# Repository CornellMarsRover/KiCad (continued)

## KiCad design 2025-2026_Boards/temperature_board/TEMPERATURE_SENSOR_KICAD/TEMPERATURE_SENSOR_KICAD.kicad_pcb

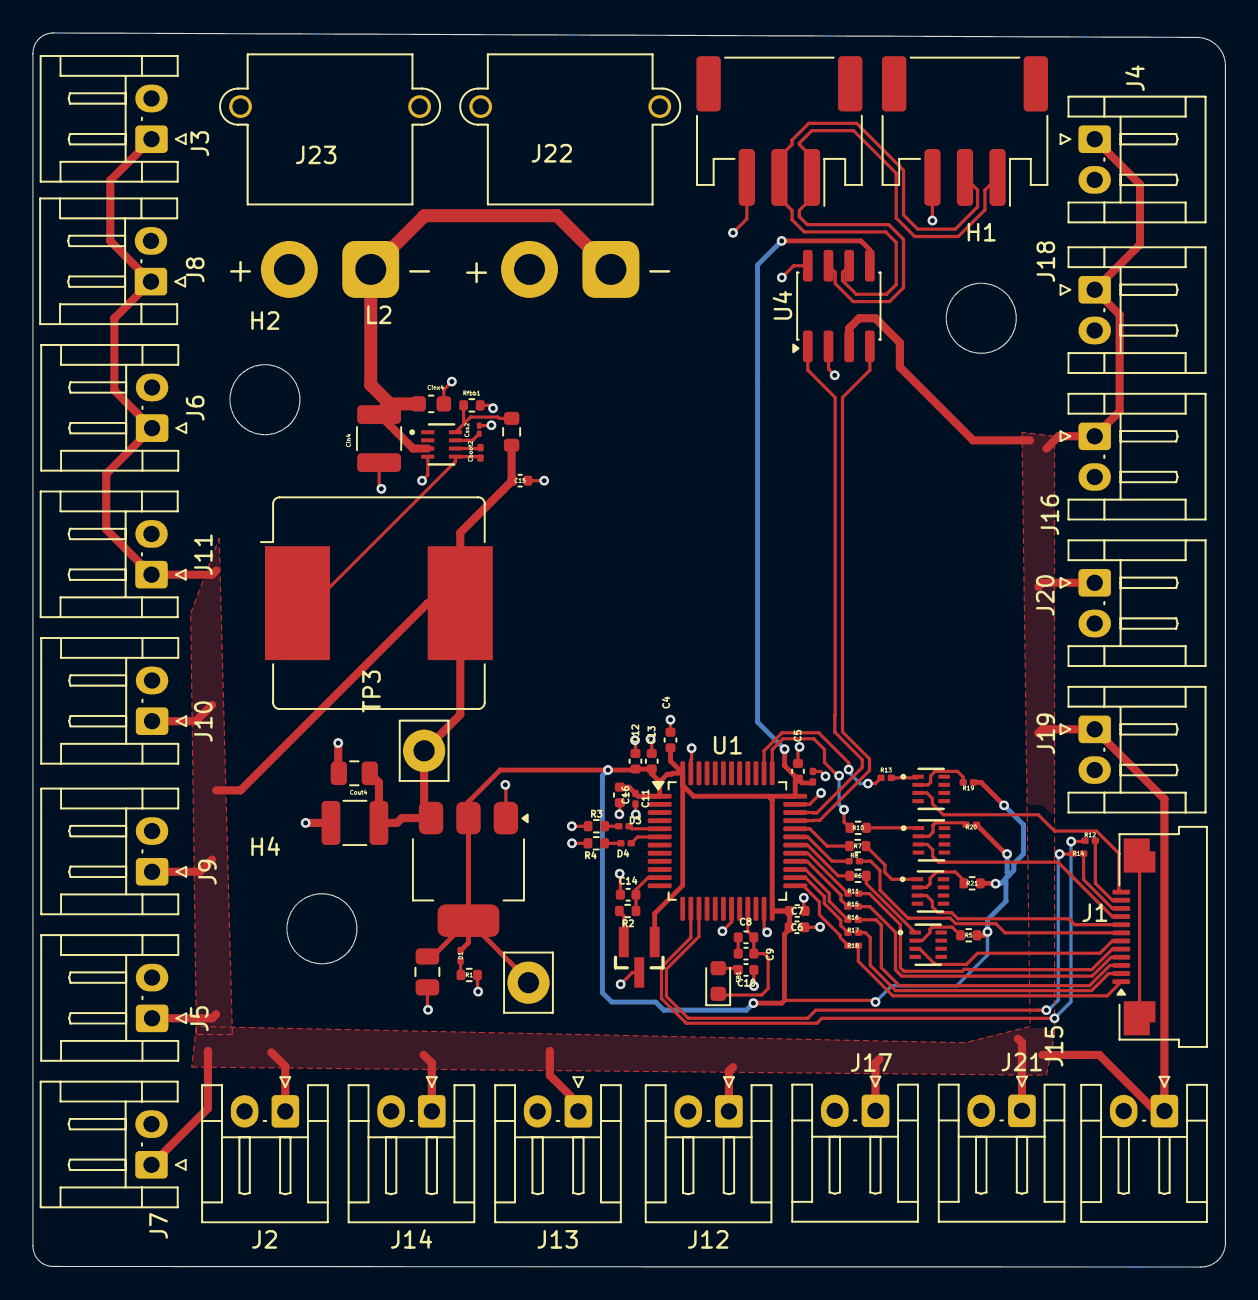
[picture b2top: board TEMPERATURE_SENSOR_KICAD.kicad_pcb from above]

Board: 2 copper layers, 73.3 x 75.8 mm, 87 parts (0 on the bottom side), 54 nets.

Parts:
C1, C2: 22u; C_0805_2012Metric
C3, C11: 10u; C_0201_0603Metric
C4, C5, C6, C7, C12, C13, C15, C16: 100n; C_0402_1005Metric
C8, C14: 10n; C_0402_1005Metric
C9, C10: 1u; C_0402_1005Metric
Cboot2: 33n; C_0201_0603Metric
Cin4: 10u; C_1210_3225Metric
Cinx4: 100n; C_0603_1608Metric
Cout4: 47u; C_1210_3225Metric
Css2: 33n; C_01005_0402Metric
D1: LED; C_0201_0603Metric
D3: DEBUG LED 1; C_0201_0603Metric
D4: DEBUG LED 2; C_0201_0603Metric
FB1: 120R; LED_0603_1608Metric
H1, H2, H4: MountingHole; MountingHole_4.3mm_M4
J1: LCD Connector Pinout; Amphenol_F32Q-1A7x1-11012_1x12-1MP_P0.5mm_Horizontal
J2, J3, J4, J5, J6, J7, J8, J9, J10, J11, J12, J13, J14, J15, J16, J17, J18, J19, J20, J21: Conn_01x02_Pin; JST_EH_S2B-EH_1x02_P2.50mm_Horizontal
J22, J23: Conn_01x02_Pin; AMASS_XT30PW-M_1x02_P2.50mm_Horizontal
J24, J25: Conn_01x03_Socket; JST_PH_S3B-PH-SM4-TB_1x03-1MP_P2.00mm_Horizontal
L2: 10u; L_Bourns_SRR1208_12.7x12.7mm
Q1, Q3, Q4: Q_NPN_BCE; SOT8_DRL_TEX
Q5: Q_PNP_BCE; SOT8_DRL_TEX
R1, R3, R4: 1k5; R_0402_1005Metric
R2, R6, R7, R10: 10k; R_0402_1005Metric
R5, R21: 55; R_0402_1005Metric
R8, R11, R12, R14, R15, R16, R17, R18: 80; R_0201_0603Metric
R13: 10k; R_0201_0603Metric
R19, R20: 55; R_0201_0603Metric
Rfbb1: 10k; R_0402_1005Metric
Rfbt1: 52.3k; R_0603_1608Metric
TP1, TP3: TestPoint; Pin_D1.3mm_L10.0mm_W3.5mm_Flat
U1: STM32G431CBT6; LQFP-48_7x7mm_P0.5mm
U2: TMP235A4DBZR; DBZ0003A-IPC_A
U3: AMS1117-3.3; SOT-223-3_TabPin2
U4: TCAN1057AEV-Q1; SOIC-8_3.9x4.9mm_P1.27mm
U5: TPS62932DRLR; SOT8_DRL_TEX-M

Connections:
5V: C1.1, C15.1, Cout4.1, J2.1, J3.1, J4.1, J5.1, J6.1, J7.1, J8.1, J9.1, J10.1, J11.1, J12.1, J13.1, J14.1, J15.1, J16.1, J17.1, J18.1, J19.1, J20.1, J21.1, L2.2, Rfbt1.1, TP3.1, U3.3 (VI), U4.3 (VCC)
28V: Cin4.1, Cinx4.1, J22.1, J23.1, U5.3 (VIN)
+3.3V: C2.1, C3.1, C4.1, C5.1, C6.1, C7.1, C11.1, C12.1, C13.1, C16.1, D1.2 (A), R5.1, R19.1, R20.1, R21.1, TP1.1, U1.1 (VBAT), U1.24 (VDD), U1.36 (VDD), U1.48 (VDD), U2.1 (VDD), U3.2 (VO), U4.5 (VIO)
+3.3VA: C8.1, C9.1, FB1.1, U1.21 (VDDA)
/PWR_LED_K: D1.1 (K), R1.1
CAN+: J24.1, J25.1, U4.7 (CANH)
CAN-: J24.2, J25.2, U4.6 (CANL)
FDCAN_+: U1.34 (PA12), U4.1 (TXD)
FDCAN_-: U1.33 (PA11), U4.4 (RXD)
GND: C1.2, C2.2, C3.2, C4.2, C5.2, C6.2, C7.2, C10.2, C11.2, C12.2, C13.2, C14.1, C15.2, C16.2, Cin4.2, Cinx4.2, Cout4.2, Css2.2, J2.2, J3.2, J4.2, J5.2, J6.2, J7.2, J8.2, J9.2, J10.2, J11.2, J12.2, J13.2, J14.2, J15.2, J16.2, J17.2, J18.2, J19.2, J20.2, J21.2, J22.2, J23.2, J24.3, J25.3, R1.2, R3.2, R4.2, Rfbb1.2, U1.19 (VSSA), U1.23 (VSS), U1.35 (VSS), U1.47 (VSS), U2.3 (GND), U3.1 (GND), U4.2 (GND), U4.8 (STB), U5.4 (GND)
unnamed: C8.2, C9.2
unnamed: C10.1, FB1.2
unnamed: D3.2 (A), U1.5 (PF0)
unnamed: D3.1 (K), R3.1
unnamed: D4.2 (A), U1.6 (PF1)
unnamed: D4.1 (K), R4.1
unnamed: J1.1, R18.2
unnamed: J1.2, R17.2
unnamed: J1.3, R16.2
unnamed: J1.4, R15.2
unnamed: J1.5, R11.2
unnamed: J1.6, Q1.3 (E)
unnamed: J1.7, R8.2
unnamed: J1.8, Q3.3 (E)
unnamed: J1.9, Q4.3 (E)
unnamed: J1.10, R14.2
unnamed: J1.11, R12.2
unnamed: J1.12, Q5.3 (E)
unnamed: Q1.1 (B), R6.2
unnamed: Q1.2 (C), R5.2
unnamed: Q3.1 (B), R7.2
unnamed: Q3.2 (C), R21.2
unnamed: Q4.1 (B), R10.2
unnamed: Q4.2 (C), R20.2
unnamed: Q5.1 (B), R13.2
unnamed: Q5.2 (C), R19.2
unnamed: C14.2, R2.1, U1.11 (PA3)
unnamed: R12.1, U1.14 (PA6)
unnamed: R14.1, U1.15 (PA7)
unnamed: R6.1, U1.30 (PA8)
unnamed: R8.1, U1.31 (PA9)
unnamed: R7.1, U1.32 (PA10)
unnamed: R10.1, U1.37 (PA13)
unnamed: R13.1, U1.38 (PA14)
unnamed: R18.1, U1.25 (PB11)
unnamed: R17.1, U1.26 (PB12)
unnamed: R16.1, U1.27 (PB13)
unnamed: R15.1, U1.28 (PB14)
unnamed: R11.1, U1.29 (PB15)
unnamed: R2.2, U2.2 (VOUT)
unnamed: Cboot2.1, U5.6 (BST)
unnamed: Rfbb1.1, Rfbt1.2, U5.8 (FB)
unnamed: Css2.1, U5.7 (SS)
unnamed: Cboot2.2, L2.1, U5.5 (SW)

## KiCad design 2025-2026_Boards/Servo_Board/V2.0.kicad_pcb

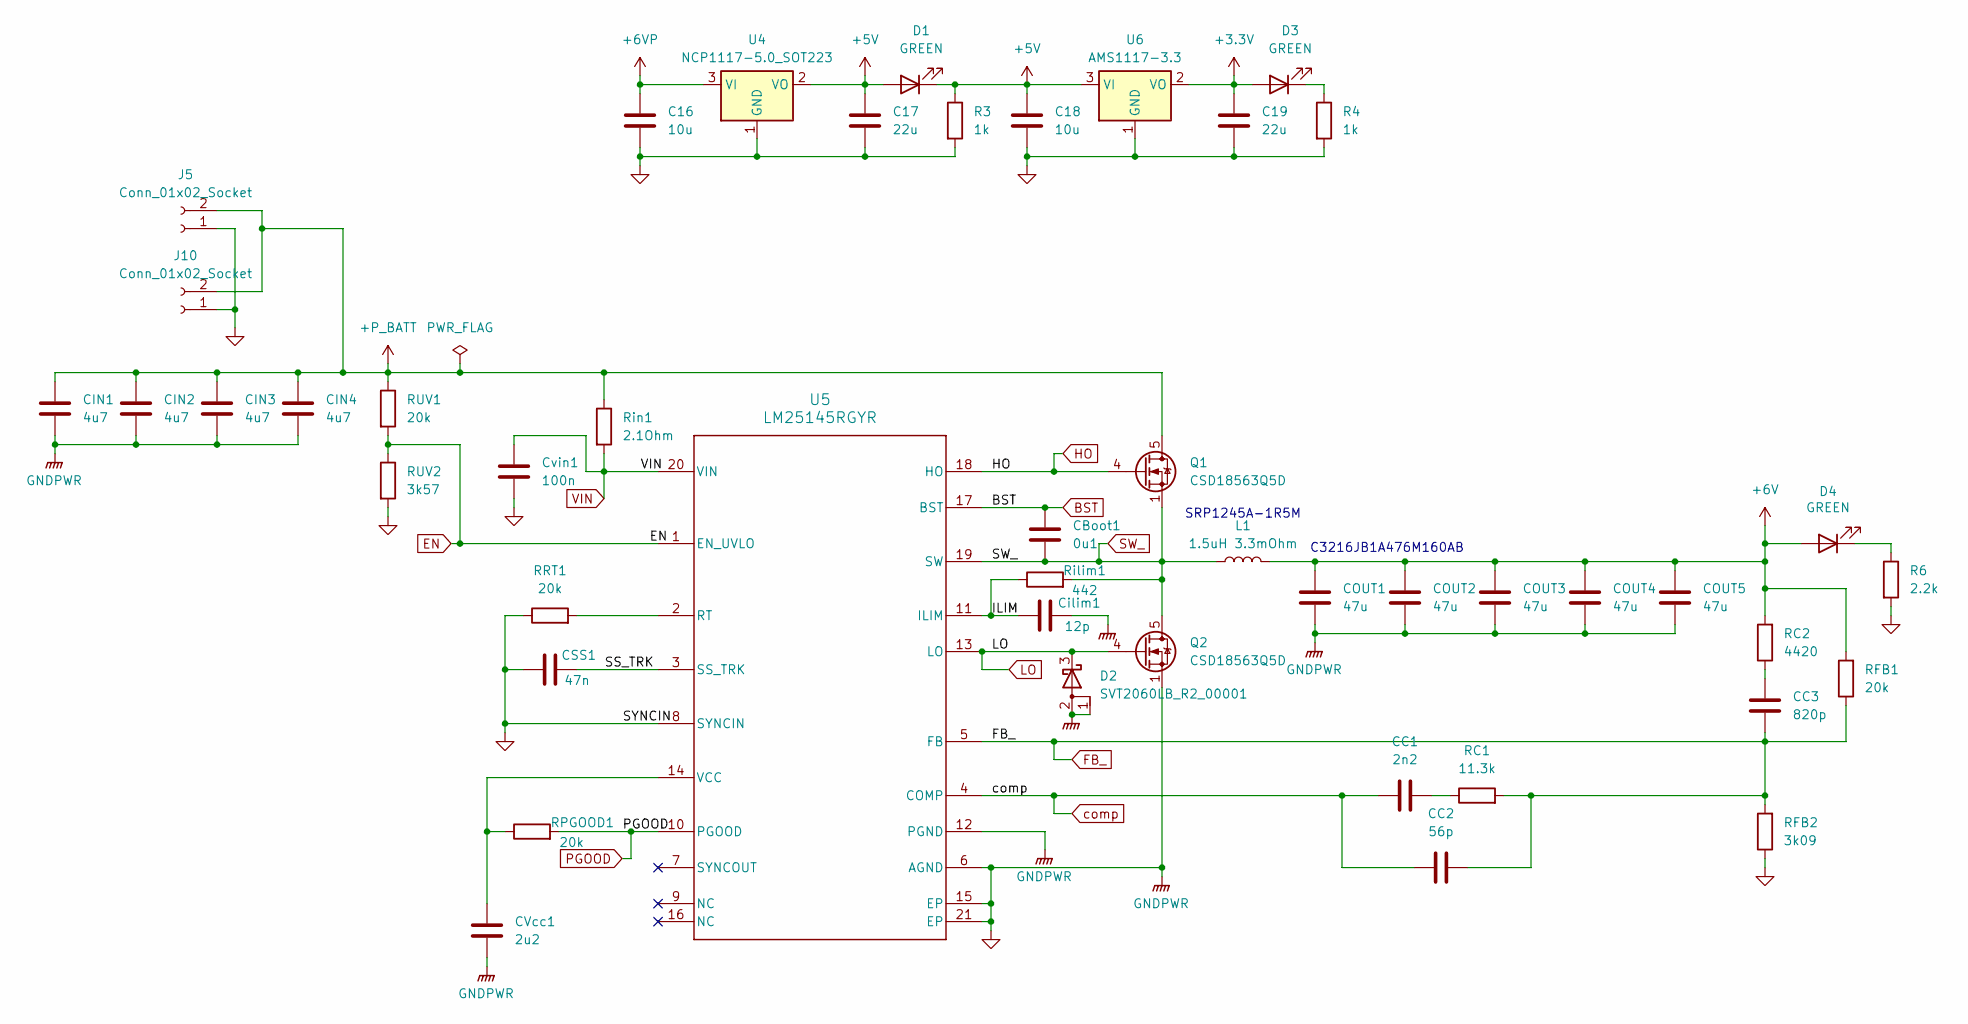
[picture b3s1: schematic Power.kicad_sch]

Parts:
C16, C18: 10u; C_0805_2012Metric
C17, C19: 22u; C_0805_2012Metric
CBoot1: 0u1; C_0603_1608Metric
CC1: 2n2; C_0402_1005Metric
CC2: 56p; C_0402_1005Metric
CC3: 820p; C_0402_1005Metric
CIN1, CIN2, CIN3, CIN4: 4u7; C_1206_3216Metric
COUT1, COUT2, COUT3, COUT4, COUT5: 47u; C_1206_3216Metric
CSS1: 47n; C_0603_1608Metric
CVcc1: 2u2; C_0603_1608Metric
Cilim1: 12p; C_0402_1005Metric
Cvin1: 100n; C_0402_1005Metric
D1, D3, D4: GREEN; LED_0603_1608Metric
D2: SVT2060LB_R2_00001; TO-277B
J5, J10: Conn_01x02_Socket; AMASS_XT30PW-M_1x02_P2.50mm_Horizontal
L1: 1.5uH 3.3mOhm; IND_AMDLA1306Q-101M
Q1, Q2: CSD18563Q5D; TDSON-8-1
R3, R4: 1k; R_0402_1005Metric
R6: 2.2k; R_0402_1005Metric
RC1: 11.3k; R_0402_1005Metric
RC2: 4420; R_0402_1005Metric
RFB1: 20k; R_0402_1005Metric
RFB2: 3k09; R_0402_1005Metric
RPGOOD1: 20k; R_0402_1005Metric
RRT1: 20k; R_0402_1005Metric
RUV1: 20k; R_0603_1608Metric
RUV2: 3k57; R_0402_1005Metric
Rilim1: 442; R_0805_2012Metric
Rin1: 2.1Ohm; R_0402_1005Metric
U4: NCP1117-5.0_SOT223; SOT-223-3_TabPin2
U5: LM25145RGYR; RGY0020B
U6: AMS1117-3.3; SOT-223-3_TabPin2

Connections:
+3.3V: C19.1, D3.2 (A), U6.2 (VO); also elsewhere on the board
+5V: C17.1, C18.1, D1.1 (K), D1.2 (A), R3.1, U4.2 (VO), U6.3 (VI); also elsewhere on the board
+6V: COUT1.1, COUT2.1, COUT3.1, COUT4.1, COUT5.1, D4.2 (A), L1.2, RC2.2, RFB1.2; also elsewhere on the board
+6VP: C16.1, U4.3 (VI); also elsewhere on the board
+P_BATT: CIN1.1, CIN2.1, CIN3.1, CIN4.1, J5.2, J10.2, Q1.5 (D), RUV1.1, Rin1.1; also elsewhere on the board
/Power/ILIM: Cilim1.1, Rilim1.1, U5.11 (ILIM)
/Power/SS_TRK: CSS1.2, U5.3 (SS_TRK)
BST: CBoot1.1, U5.17 (BST); also elsewhere on the board
EN: RUV1.2, RUV2.1, U5.1 (EN_UVLO); also elsewhere on the board
FB_: CC2.2, CC3.1, RC1.2, RFB1.1, RFB2.2, U5.5 (FB); also elsewhere on the board
GND: C16.2, C17.2, C18.2, C19.2, CIN1.2, CIN2.2, CIN3.2, CIN4.2, COUT1.2, COUT2.2, COUT3.2, COUT4.2, COUT5.2, CSS1.1, CVcc1.2, Cilim1.2, Cvin1.2, D2.1 (A), D2.2 (A), J5.1, J10.1, Q2.1 (S), Q2.2 (S), Q2.3 (S), R3.2, R4.2, R6.2, RFB2.1, RRT1.1, RUV2.2, U4.1 (GND), U5.6 (AGND), U5.8 (SYNCIN), U5.12 (PGND), U5.15 (EP), U5.21 (EP), U6.1 (GND); also elsewhere on the board
HO: Q1.4 (G), U5.18 (HO); also elsewhere on the board
LO: D2.3 (K), Q2.4 (G), U5.13 (LO); also elsewhere on the board
unnamed: CC1.2, RC1.1
unnamed: CC3.2, RC2.1
unnamed: D3.1 (K), R4.1
unnamed: D4.1 (K), R6.1
unnamed: RRT1.2, U5.2 (RT)
unnamed: CVcc1.1, RPGOOD1.1, U5.14 (VCC)
PGOOD: RPGOOD1.2, U5.10 (PGOOD); also elsewhere on the board
SW_: CBoot1.2, L1.1, Q1.1 (S), Q1.2 (S), Q1.3 (S), Q2.5 (D), Rilim1.2, U5.19 (SW); also elsewhere on the board
VIN: Cvin1.1, Rin1.2, U5.20 (VIN); also elsewhere on the board
comp: CC1.1, CC2.1, U5.4 (COMP); also elsewhere on the board

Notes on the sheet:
SRP1245A-1R5M
C3216JB1A476M160AB

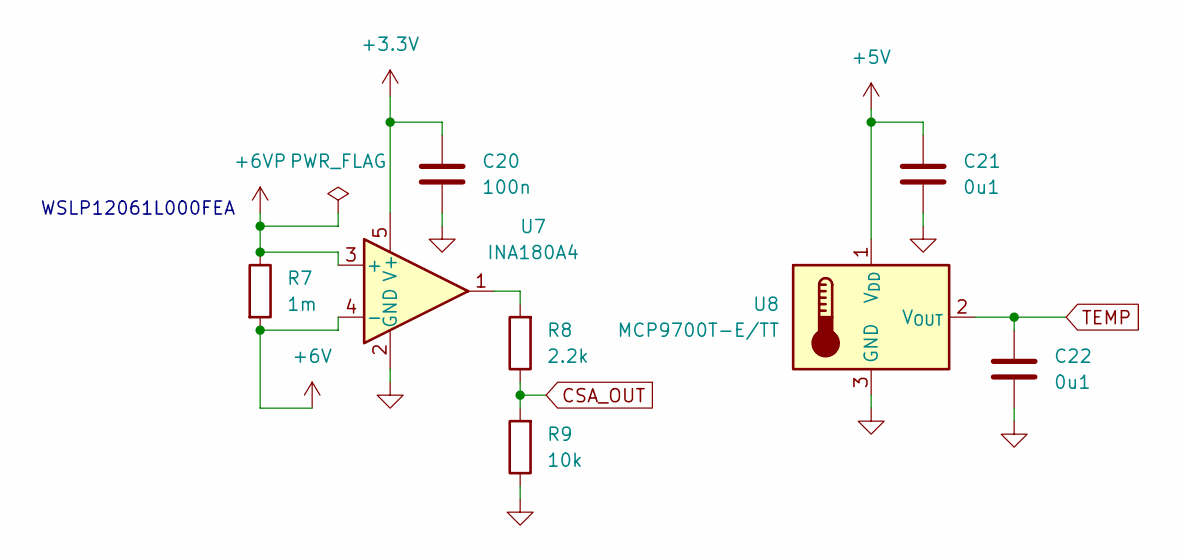
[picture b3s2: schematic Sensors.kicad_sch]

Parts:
C20: 100n; C_0402_1005Metric
C21, C22: 0u1; C_0402_1005Metric
R7: 1m; R_1206_3216Metric
R8: 2.2k; R_0402_1005Metric
R9: 10k; R_0402_1005Metric
U7: INA180A4; SOT-23-5
U8: MCP9700T-E/TT; SOT-23-3

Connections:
+3.3V: C20.1, U7.5 (V+); also elsewhere on the board
+5V: C21.1, U8.1 (V_{DD}); also elsewhere on the board
+6V: R7.2, U7.4 (-); also elsewhere on the board
+6VP: R7.1, U7.3 (+); also elsewhere on the board
CSA_OUT: R8.1, R9.2; also elsewhere on the board
GND: C20.2, C21.2, C22.2, R9.1, U7.2 (GND), U8.3 (GND); also elsewhere on the board
unnamed: R8.2, U7.1
TEMP: C22.1, U8.2 (V_{OUT}); also elsewhere on the board

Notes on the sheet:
WSLP12061L000FEA

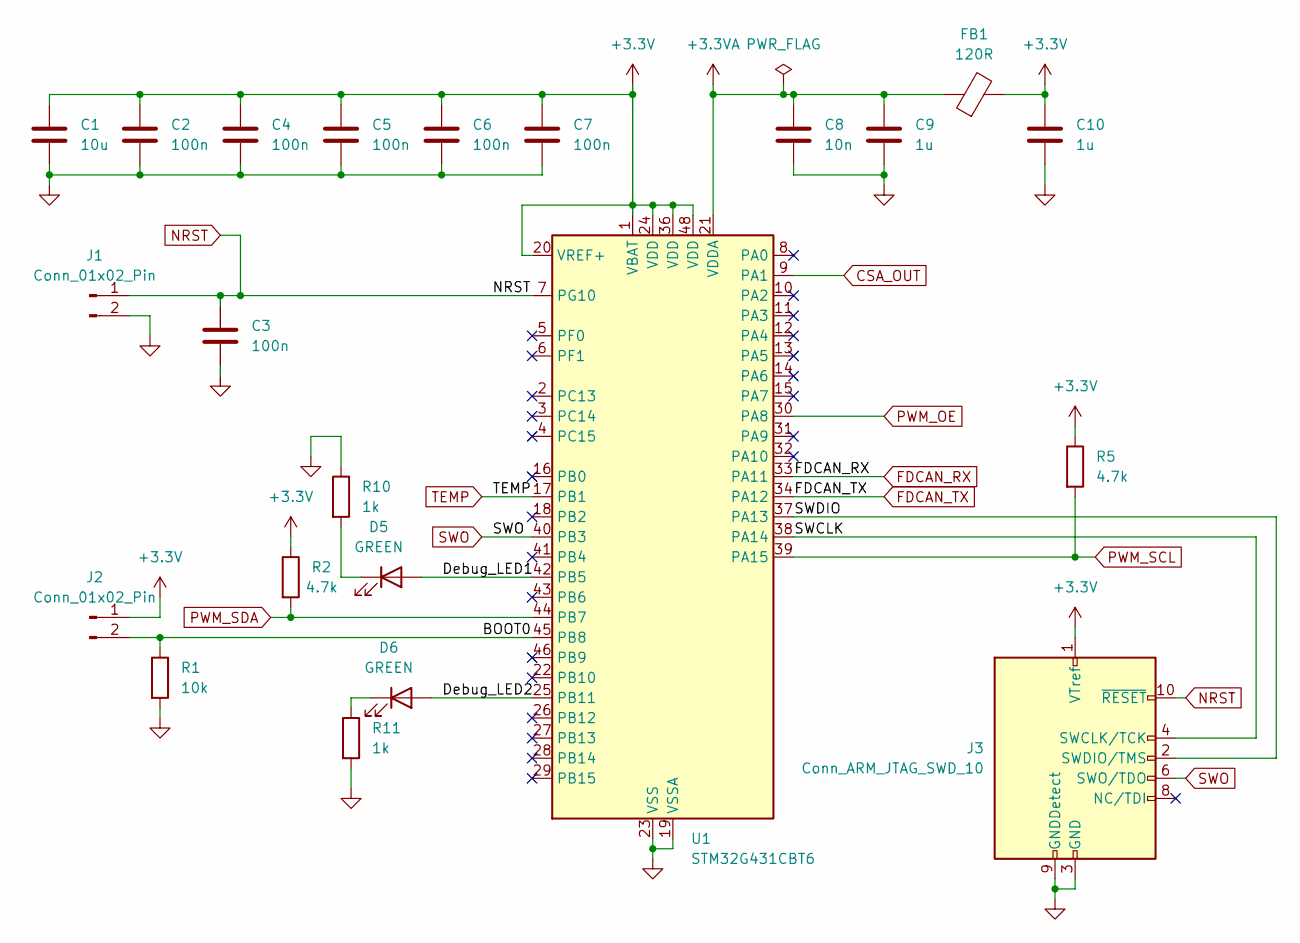
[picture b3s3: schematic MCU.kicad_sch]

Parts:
C1: 10u; C_0603_1608Metric
C2, C3, C4, C5, C6, C7: 100n; C_0402_1005Metric
C8: 10n; C_0402_1005Metric
C9, C10: 1u; C_0402_1005Metric
D5, D6: GREEN; LED_0603_1608Metric
FB1: 120R; L_0603_1608Metric
J1: Conn_01x02_Pin; PinHeader_1x02_P2.54mm_Horizontal
J2: Conn_01x02_Pin; PinHeader_1x02_P2.54mm_Vertical
J3: Conn_ARM_JTAG_SWD_10; PinHeader_2x05_P1.27mm_Vertical
R1: 10k; R_0402_1005Metric
R2, R5: 4.7k; R_0402_1005Metric
R10, R11: 1k; R_0402_1005Metric
U1: STM32G431CBT6; LQFP-48_7x7mm_P0.5mm

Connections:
+3.3V: C1.1, C2.1, C4.1, C5.1, C6.1, C7.1, C10.1, FB1.2, J2.1, J3.1 (VTref), R2.1, R5.1, U1.1 (VBAT), U1.20 (VREF+), U1.24 (VDD), U1.36 (VDD), U1.48 (VDD); also elsewhere on the board
+3.3VA: C8.1, C9.1, FB1.1, U1.21 (VDDA)
/MCU/BOOT0: J2.2, R1.1, U1.45 (PB8)
/MCU/Debug_LED1: D5.2 (A), U1.42 (PB5)
/MCU/Debug_LED2: D6.2 (A), U1.25 (PB11)
/MCU/SWCLK: J3.4 (SWCLK/TCK), U1.38 (PA14)
/MCU/SWDIO: J3.2 (SWDIO/TMS), U1.37 (PA13)
CSA_OUT: U1.9 (PA1); also elsewhere on the board
FDCAN_RX: U1.33 (PA11); also elsewhere on the board
FDCAN_TX: U1.34 (PA12); also elsewhere on the board
GND: C1.2, C2.2, C3.2, C4.2, C5.2, C6.2, C7.2, C8.2, C9.2, C10.2, J1.2, J3.3 (GND), J3.5 (GND), J3.9 (GNDDetect), R1.2, R10.1, R11.2, U1.19 (VSSA), U1.23 (VSS), U1.35 (VSS), U1.47 (VSS); also elsewhere on the board
NRST: C3.1, J1.1, J3.10 (~RESET), U1.7 (PG10); also elsewhere on the board
unnamed: D5.1 (K), R10.2
unnamed: D6.1 (K), R11.1
PWM_OE: U1.30 (PA8); also elsewhere on the board
PWM_SCL: R5.2, U1.39 (PA15); also elsewhere on the board
PWM_SDA: R2.2, U1.44 (PB7); also elsewhere on the board
SWO: J3.6 (SWO/TDO), U1.40 (PB3)
TEMP: U1.17 (PB1); also elsewhere on the board

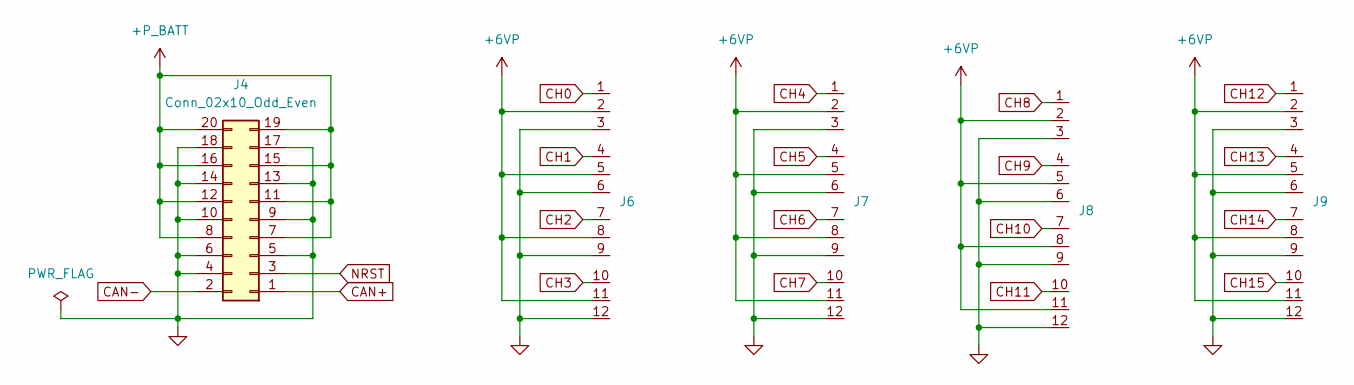
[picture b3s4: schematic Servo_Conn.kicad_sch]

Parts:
J4: Conn_02x10_Odd_Even; PinSocket_2x10_P2.54mm_Horizontal
J6, J7, J8, J9: Conn_03x4

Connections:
+6VP: J6.2, J6.5, J6.8, J6.11, J7.2, J7.5, J7.8, J7.11, J8.2, J8.5, J8.8, J8.11, J9.2, J9.5, J9.8, J9.11; also elsewhere on the board
+P_BATT: J4.7, J4.8, J4.11, J4.12, J4.15, J4.16, J4.19, J4.20; also elsewhere on the board
CAN+: J4.1; also elsewhere on the board
CAN-: J4.2; also elsewhere on the board
CH0: J6.1; also elsewhere on the board
CH1: J6.4; also elsewhere on the board
CH2: J6.7; also elsewhere on the board
CH3: J6.10; also elsewhere on the board
CH4: J7.1; also elsewhere on the board
CH5: J7.4; also elsewhere on the board
CH6: J7.7; also elsewhere on the board
CH7: J7.10; also elsewhere on the board
CH8: J8.1; also elsewhere on the board
CH9: J8.4; also elsewhere on the board
CH10: J8.7; also elsewhere on the board
CH11: J8.10; also elsewhere on the board
CH12: J9.1; also elsewhere on the board
CH13: J9.4; also elsewhere on the board
CH14: J9.7; also elsewhere on the board
CH15: J9.10; also elsewhere on the board
GND: J4.4, J4.5, J4.6, J4.9, J4.10, J4.13, J4.14, J4.17, J4.18, J6.3, J6.6, J6.9, J6.12, J7.3, J7.6, J7.9, J7.12, J8.3, J8.6, J8.9, J8.12, J9.3, J9.6, J9.9, J9.12; also elsewhere on the board
NRST: J4.3; also elsewhere on the board

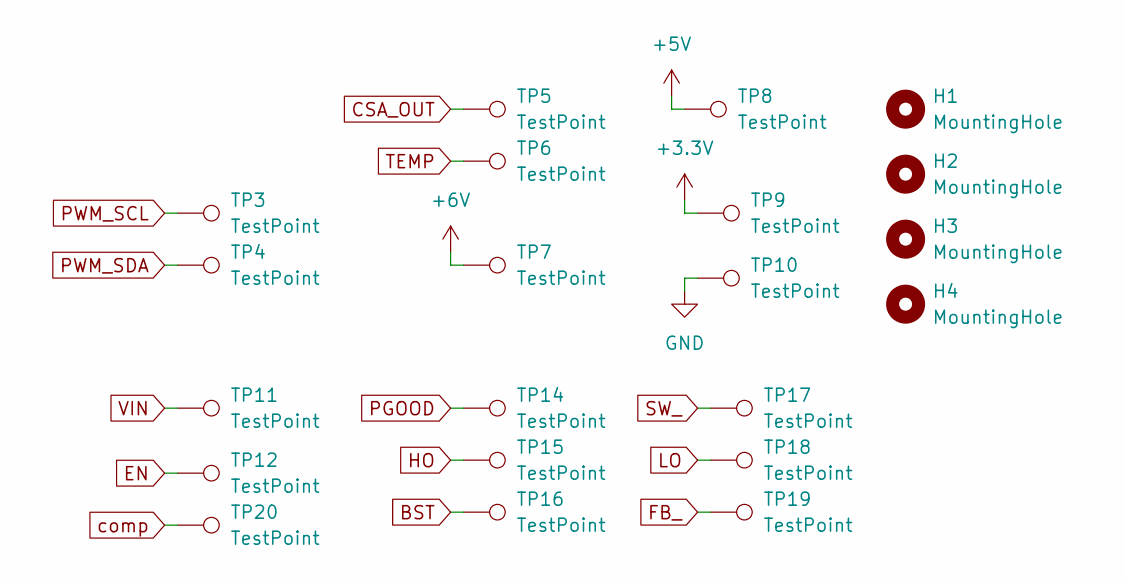
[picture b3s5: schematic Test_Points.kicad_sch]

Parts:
H1, H2, H3, H4: MountingHole; MountingHole_2.7mm_M2.5
TP3, TP4, TP5, TP6, TP7, TP8, TP9, TP10, TP11, TP12, TP14, TP15, TP16, TP17, TP18, TP19, TP20: TestPoint; TestPoint_Pad_D1.0mm

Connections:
+3.3V: TP9.1; also elsewhere on the board
+5V: TP8.1; also elsewhere on the board
+6V: TP7.1; also elsewhere on the board
BST: TP16.1; also elsewhere on the board
CSA_OUT: TP5.1; also elsewhere on the board
EN: TP12.1; also elsewhere on the board
FB_: TP19.1; also elsewhere on the board
GND: TP10.1; also elsewhere on the board
HO: TP15.1; also elsewhere on the board
LO: TP18.1; also elsewhere on the board
PGOOD: TP14.1; also elsewhere on the board
PWM_SCL: TP3.1; also elsewhere on the board
PWM_SDA: TP4.1; also elsewhere on the board
SW_: TP17.1; also elsewhere on the board
TEMP: TP6.1; also elsewhere on the board
VIN: TP11.1; also elsewhere on the board
comp: TP20.1; also elsewhere on the board

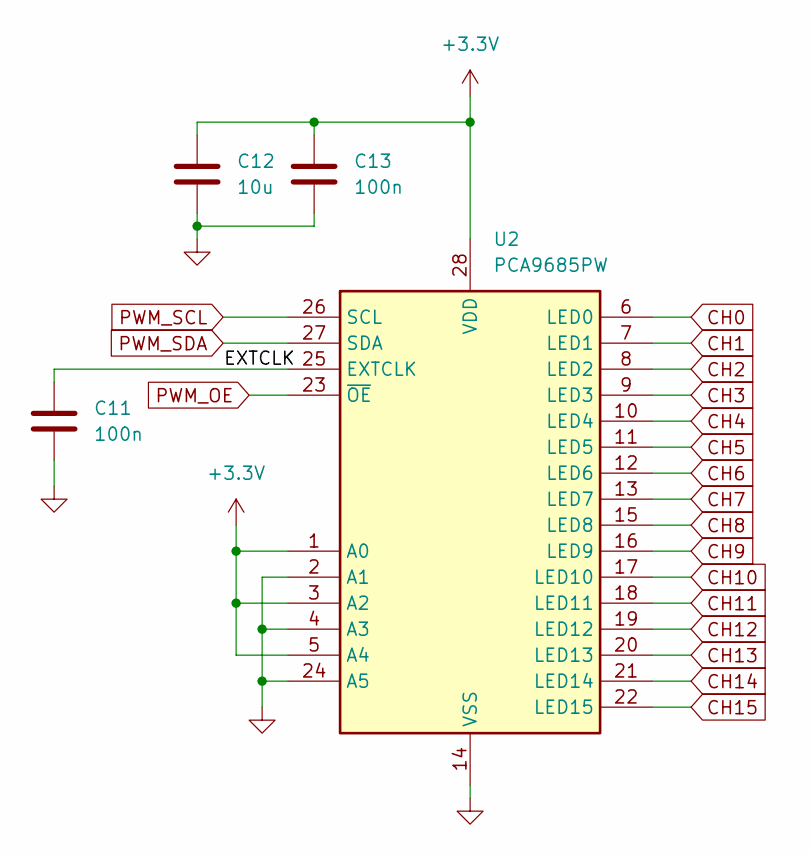
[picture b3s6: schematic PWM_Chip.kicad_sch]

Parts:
C11, C13: 100n; C_0402_1005Metric
C12: 10u; C_0603_1608Metric
U2: PCA9685PW; TSSOP-28_4.4x9.7mm_P0.65mm

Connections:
+3.3V: C12.1, C13.1, U2.1 (A0), U2.3 (A2), U2.5 (A4), U2.28 (VDD); also elsewhere on the board
/PWM Chip/EXTCLK: C11.1, U2.25 (EXTCLK)
CH0: U2.6 (LED0); also elsewhere on the board
CH1: U2.7 (LED1); also elsewhere on the board
CH2: U2.8 (LED2); also elsewhere on the board
CH3: U2.9 (LED3); also elsewhere on the board
CH4: U2.10 (LED4); also elsewhere on the board
CH5: U2.11 (LED5); also elsewhere on the board
CH6: U2.12 (LED6); also elsewhere on the board
CH7: U2.13 (LED7); also elsewhere on the board
CH8: U2.15 (LED8); also elsewhere on the board
CH9: U2.16 (LED9); also elsewhere on the board
CH10: U2.17 (LED10); also elsewhere on the board
CH11: U2.18 (LED11); also elsewhere on the board
CH12: U2.19 (LED12); also elsewhere on the board
CH13: U2.20 (LED13); also elsewhere on the board
CH14: U2.21 (LED14); also elsewhere on the board
CH15: U2.22 (LED15); also elsewhere on the board
GND: C11.2, C12.2, C13.2, U2.2 (A1), U2.4 (A3), U2.14 (VSS), U2.24 (A5); also elsewhere on the board
PWM_OE: U2.23 (~OE); also elsewhere on the board
PWM_SCL: U2.26 (SCL); also elsewhere on the board
PWM_SDA: U2.27 (SDA); also elsewhere on the board

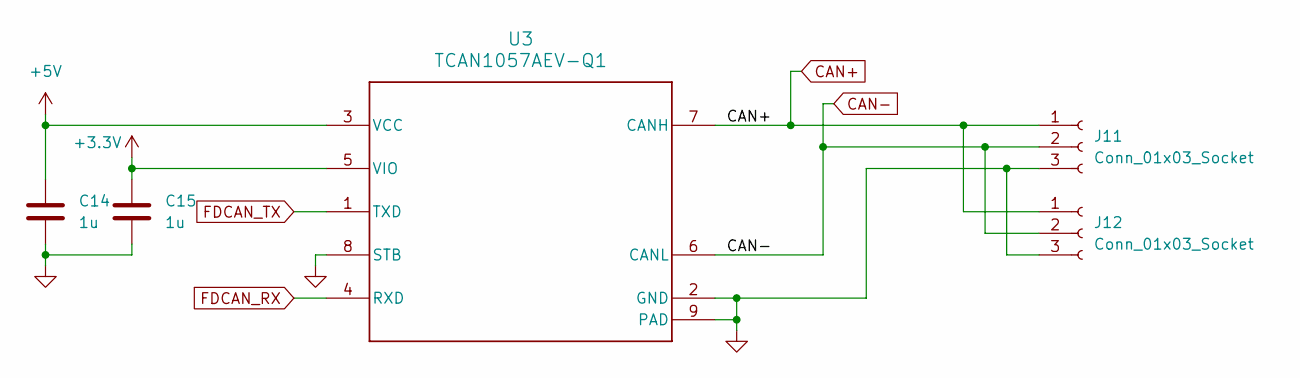
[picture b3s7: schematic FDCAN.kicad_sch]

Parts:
C14, C15: 1u; C_0402_1005Metric
J11, J12: Conn_01x03_Socket; JST_PH_S3B-PH-SM4-TB_1x03-1MP_P2.00mm_Horizontal
U3: TCAN1057AEV-Q1; SOIC-8_3.9x4.9mm_P1.27mm; MPN TCAN1057AEVDRQ1

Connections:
+3.3V: C15.1, U3.5 (VIO); also elsewhere on the board
+5V: C14.1, U3.3 (VCC); also elsewhere on the board
CAN+: J11.1, J12.1, U3.7 (CANH); also elsewhere on the board
CAN-: J11.2, J12.2, U3.6 (CANL); also elsewhere on the board
FDCAN_RX: U3.4 (RXD); also elsewhere on the board
FDCAN_TX: U3.1 (TXD); also elsewhere on the board
GND: C14.2, C15.2, J11.3, J12.3, U3.2 (GND), U3.8 (STB), U3.9 (PAD); also elsewhere on the board

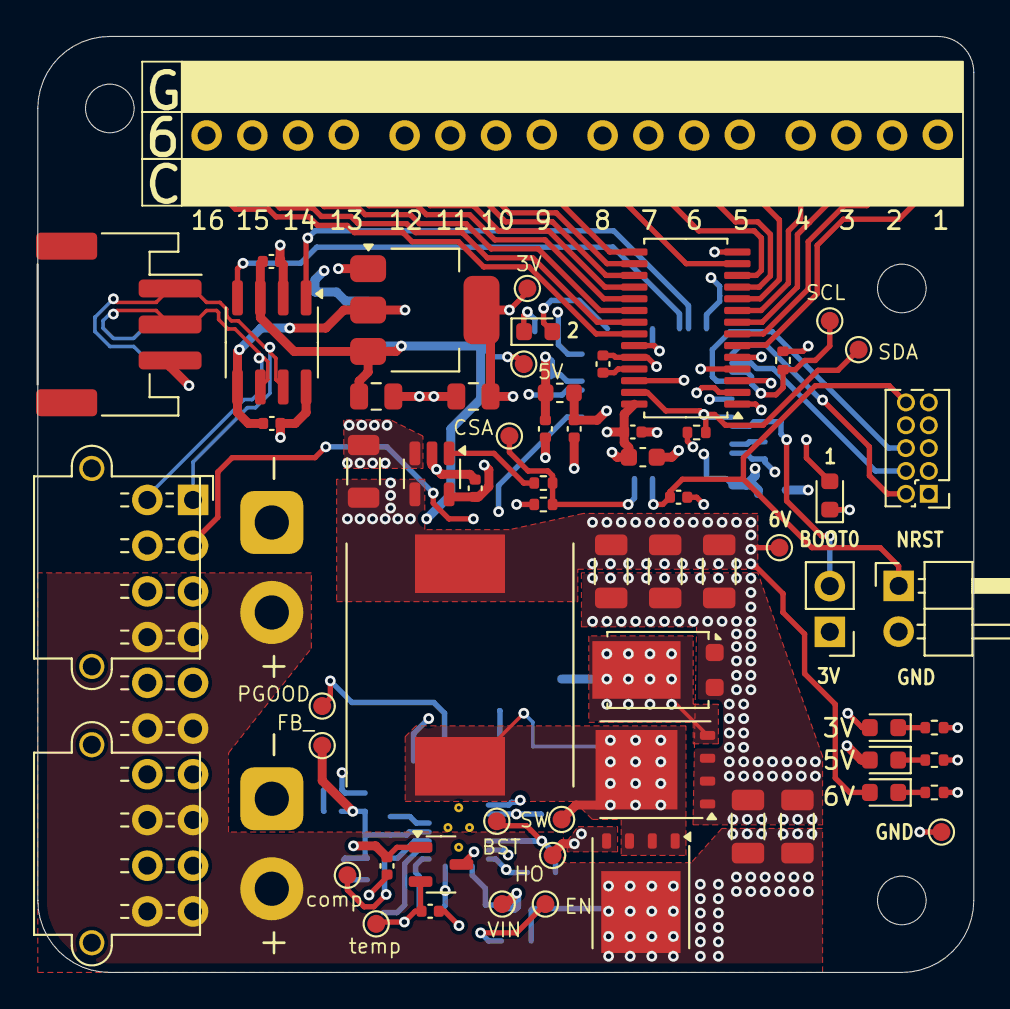
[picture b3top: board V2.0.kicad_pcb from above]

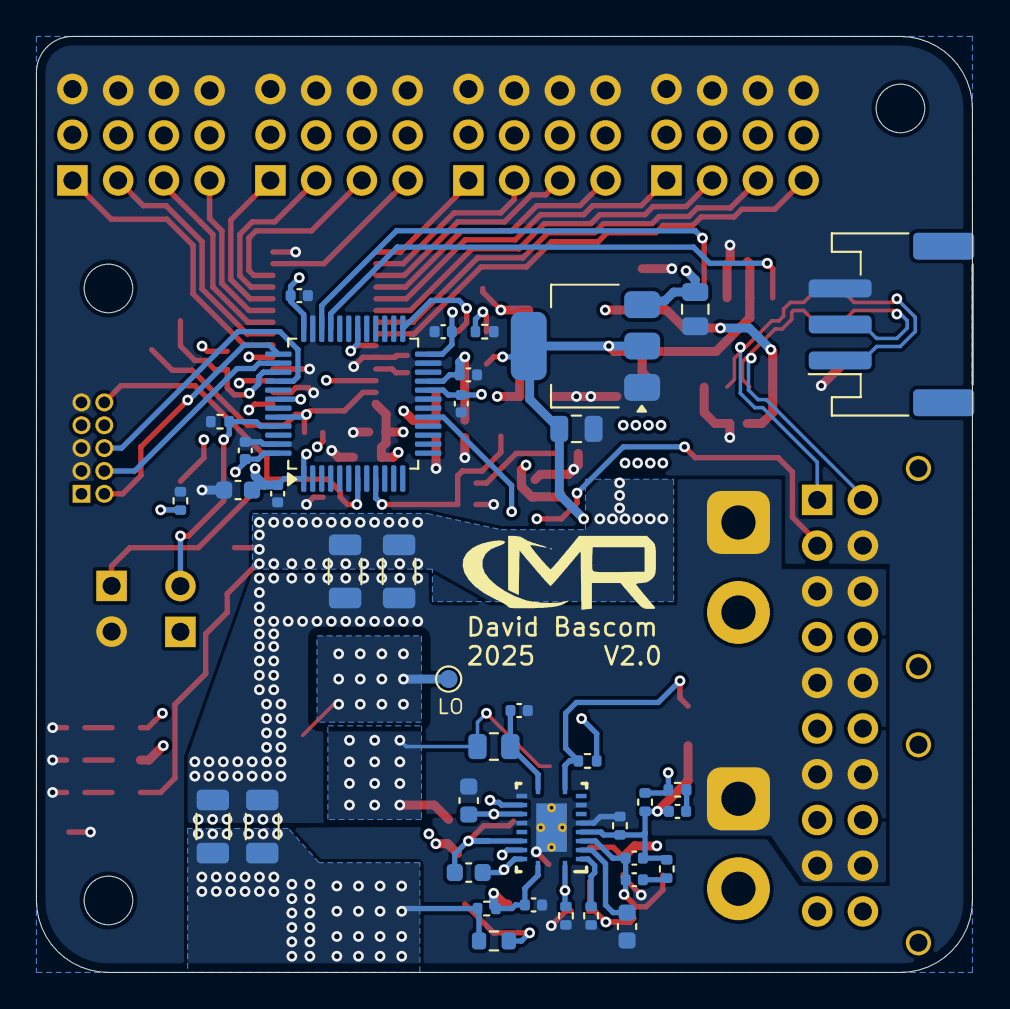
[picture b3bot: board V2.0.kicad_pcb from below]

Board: 4 copper layers, 52.0 x 52.0 mm, 110 parts (39 on the bottom side), 60 nets.

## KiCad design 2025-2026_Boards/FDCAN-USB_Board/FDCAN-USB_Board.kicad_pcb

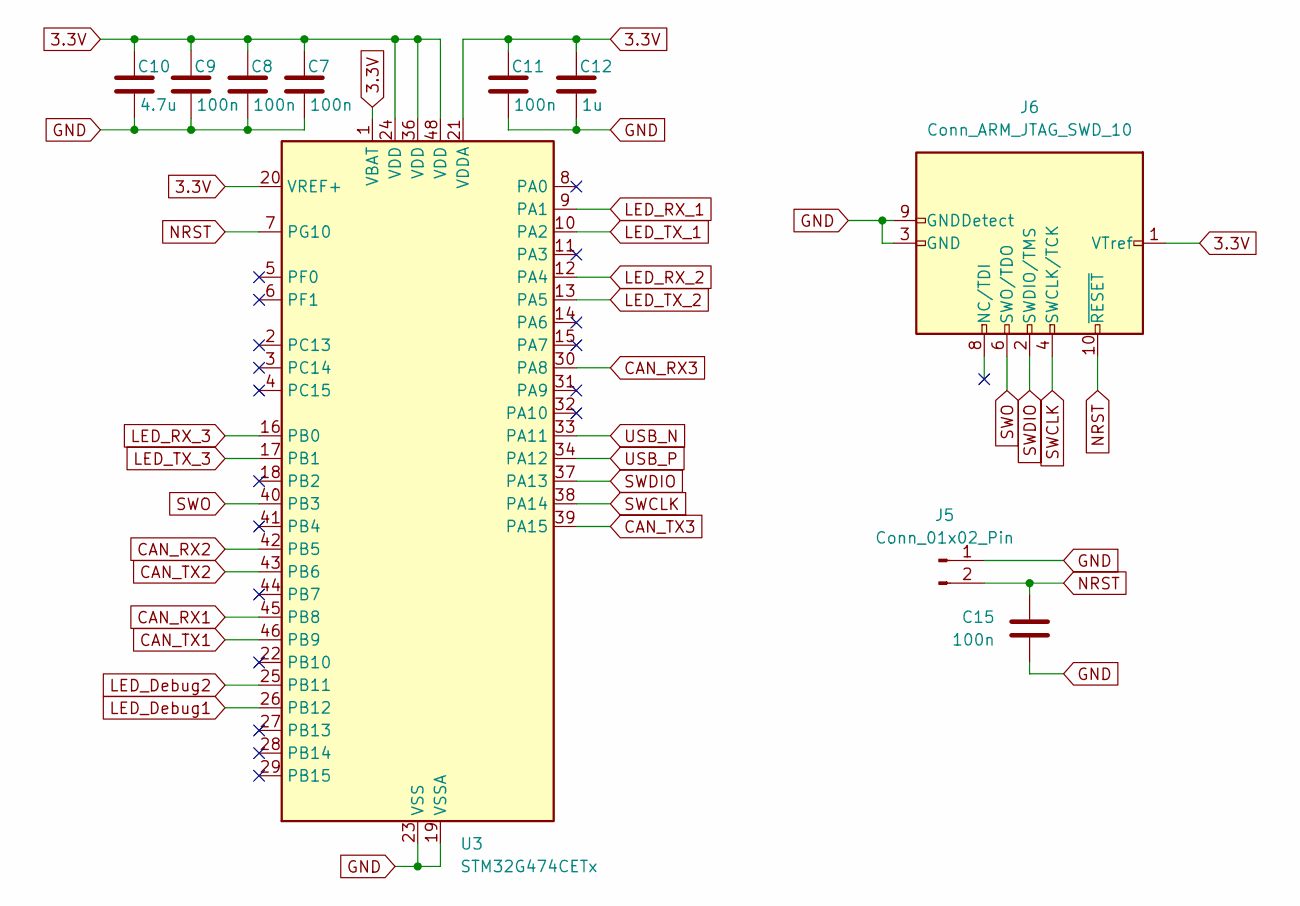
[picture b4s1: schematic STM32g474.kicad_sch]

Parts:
C7, C8, C9, C11, C15: 100n; C_0402_1005Metric
C10: 4.7u; C_0603_1608Metric
C12: 1u; C_0402_1005Metric
J5: Conn_01x02_Pin; PinHeader_1x02_P2.54mm_Vertical
J6: Conn_ARM_JTAG_SWD_10; PinHeader_2x05_P1.27mm_Vertical
U3: STM32G474CETx; LQFP-48_7x7mm_P0.5mm

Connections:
3.3V: C7.1, C8.1, C9.1, C10.1, C11.1, C12.1, J6.1 (VTref), U3.1 (VBAT), U3.20 (VREF+), U3.21 (VDDA), U3.24 (VDD), U3.36 (VDD), U3.48 (VDD); also elsewhere on the board
CAN_RX1: U3.45 (PB8); also elsewhere on the board
CAN_RX2: U3.42 (PB5); also elsewhere on the board
CAN_RX3: U3.30 (PA8); also elsewhere on the board
CAN_TX1: U3.46 (PB9); also elsewhere on the board
CAN_TX2: U3.43 (PB6); also elsewhere on the board
CAN_TX3: U3.39 (PA15); also elsewhere on the board
GND: C7.2, C8.2, C9.2, C10.2, C11.2, C12.2, C15.2, J5.1, J6.3 (GND), J6.5 (GND), J6.9 (GNDDetect), U3.19 (VSSA), U3.23 (VSS), U3.35 (VSS), U3.47 (VSS); also elsewhere on the board
LED_Debug1: U3.26 (PB12); also elsewhere on the board
LED_Debug2: U3.25 (PB11); also elsewhere on the board
LED_RX_1: U3.9 (PA1); also elsewhere on the board
LED_RX_2: U3.12 (PA4); also elsewhere on the board
LED_RX_3: U3.16 (PB0); also elsewhere on the board
LED_TX_1: U3.10 (PA2); also elsewhere on the board
LED_TX_2: U3.13 (PA5); also elsewhere on the board
LED_TX_3: U3.17 (PB1); also elsewhere on the board
NRST: C15.1, J5.2, J6.10 (~RESET), U3.7 (PG10)
SWCLK: J6.4 (SWCLK/TCK), U3.38 (PA14)
SWDIO: J6.2 (SWDIO/TMS), U3.37 (PA13)
SWO: J6.6 (SWO/TDO), U3.40 (PB3)
USB_N: U3.33 (PA11); also elsewhere on the board
USB_P: U3.34 (PA12); also elsewhere on the board

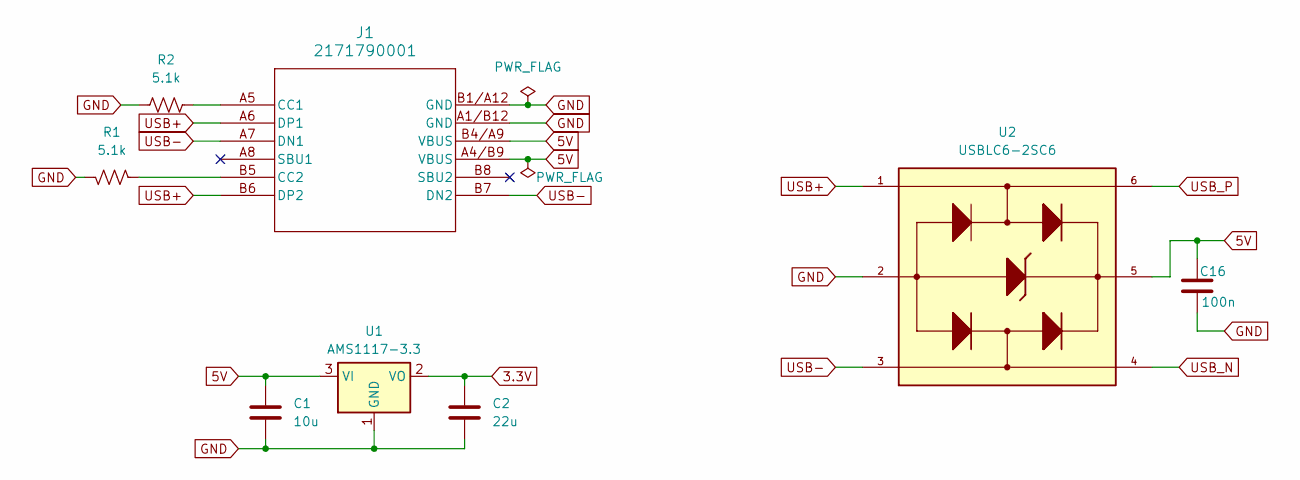
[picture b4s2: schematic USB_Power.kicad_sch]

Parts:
C1: 10u; C_0805_2012Metric
C2: 22u; C_0805_2012Metric
C16: 100n; C_0402_1005Metric
J1: 2171790001; 2171790001_MOL
R1, R2: 5.1k; R_0603_1608Metric
U1: AMS1117-3.3; SOT-223-3_TabPin2
U2: USBLC6-2SC6; SOT95P280X145-6N

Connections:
3.3V: C2.1, U1.2 (VO); also elsewhere on the board
5V: C1.1, C16.1, J1.A4/B9 (VBUS), J1.B4/A9 (VBUS), U1.3 (VI), U2.5; also elsewhere on the board
GND: C1.2, C2.2, C16.2, J1.A1/B12 (GND), J1.B1/A12 (GND), R1.1, R2.2, U1.1 (GND), U2.2; also elsewhere on the board
unnamed: J1.A5 (CC1), R2.1
unnamed: J1.B5 (CC2), R1.2
USB+: J1.A6 (DP1), J1.B6 (DP2), U2.1
USB-: J1.A7 (DN1), J1.B7 (DN2), U2.3
USB_N: U2.4; also elsewhere on the board
USB_P: U2.6; also elsewhere on the board
